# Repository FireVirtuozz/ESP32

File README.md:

# ESP32 RC car and Rust ground station

A 1/10 RC car (Supra MK5 body, 3D printed chassis) built from scratch: a custom PCB, two ESP32-S3 running C firmware (ESP-IDF), and a Rust ground station that drives the car, shows the sensors and builds a 2D map (SLAM).

## What it does

- **Drive** the car with a gamepad over Wi-Fi (UDP), with configurable acceleration profiles, an emergency brake and front / rear obstacle blocking
- **Sense**: IMU, lidar, ToF, ultrasonic, GNSS, camera (JPG stream), wheel encoder, battery voltage and motor current
- **Ground station** (laptop): egui GUI, record and replay, OTA updates, odometry, 2D SLAM (NDT and ICP)
- **Remote**: a Tailscale relay forwards the data without the GUI

## How it fits together

```
 sensors / motor / servo
          |
   custom PCB (KiCad)
          |
  ESP32-S3 control (C, ESP-IDF) --.
                                   >--- UDP over Wi-Fi ---> rust_station (laptop, egui)
  ESP32-S3 camera  (C, ESP-IDF) --'                          |  odometry, SLAM, record / replay
          ^                                                   |
          '------------- commands (gamepad, every 30 ms) -----'
```

## Repo

| Folder | Content |
|---|---|
| [`esp_project`](esp_project) | ESP-IDF firmware (C): the libraries and the car firmware |
| [`rust_station`](rust_station) | Rust ground station ([`station`](rust_station/station)) and AI training ([`train_ia`](rust_station/train_ia)) |
| [`hardware`](hardware) | KiCad project of the PCB, power and wiring |

The same ESP-IDF libraries were also used for a Zigbee home hub (ESP32-C6). They are easy to reuse to test sensors, MQTT, OTA, ESP-NOW, encryption or Wi-Fi.

## Hardware

| Part | Model |
|---|---|
| Body / chassis | Supra MK5 1/10, 3D printed chassis (Dukedoks design), full PLA |
| Battery | LiPo 7.3 V, 3000 mAh, 25C |
| Motor / driver | Brushed 550 (21T), BTS7960 H-bridge |
| Steering | MG996R servo |
| Boards | ESP32-S3 N16R8 (control), ESP32-S3 (camera) |
| Camera | OV5640, 120° lens <!-- TODO: check, it was in the TODO list of my notes --> |
| Sensors | BNO085 IMU, D500 lidar, BZ181 GNSS, TOF400C (front), HC-SR04 (front / rear), ACS758 50 A current sensor, FC-33 optical encoder |
| Other | KY-006 passive buzzer, 2x Mini560 Pro buck converters (5 V / 3.3 V) |

Power and wiring details are in [`hardware`](hardware).

## Status

| Done | In progress / planned |
|---|---|
| UDP control and telemetry, OTA | Check the camera with sleep / framerate |
| Acceleration profiles, emergency brake | Wi-Fi hotspot setup, cleaner logs |
| Odometry (IMU + encoder) | Chunked grid, better log-odds |
| 2D SLAM (NDT, ICP) | Sensor fusion (accelerometer / odometry / camera) to detect and correct slipping |
| Record and replay | Second, phase-shifted encoder to get the direction |
| egui GUI, Tailscale relay | Pure Pursuit with waypoints |
| ESP-NOW library (not used on the car yet) | Exploration algorithm on the grid |
| | Rear camera |
| | AI for control |
| | Custom controller (ESP-NOW) |
| | Real Tamiya TT02 chassis, new clean body (PETG / clear PETG / TPU) |

## Docker (ESP-IDF)

You can use the minimal Dockerfile of this repo (Windows-friendly) or the one from [Espressif](https://github.com/espressif/esp-idf/blob/master/tools/docker/Dockerfile).

```bash
docker build -t esp32-idf .
docker run -it --rm --network host --device=/dev/ttyUSB0 -v $(pwd):/workspace esp32-idf
```

<details>
<summary>Windows + WSL (USB passthrough)</summary>

Share the USB device from Windows to WSL:

```bash
ls /dev/ttyUSB*
usbipd list
usbipd bind --busid 2-3
usbipd attach --wsl --busid 2-3
```

Then launch the container from PowerShell:

```bash
usbipd attach --wsl --busid 2-3

# using /mnt/c from WSL (works, but slow)
cd D:\ESP32
wsl
docker run -it --rm --network host --device=/dev/ttyUSB0 -v $(pwd):/workspace esp32-idf

# better for performance: stay inside WSL and sync files with GitHub
wsl
cd ~/projects/ESP32
docker run -it --rm --network host -v $(pwd):/workspace esp32-idf:latest
```

</details>

## Run the station

See [`rust_station`](rust_station) for the details of the station.

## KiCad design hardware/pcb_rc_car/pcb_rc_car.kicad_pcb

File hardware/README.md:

# hardware

KiCad project of the PCB of the RC car, with the power and wiring of the car.

<!-- TODO: add the schematic (PDF or PNG) and a render of the PCB here -->

## Files

<!-- TODO: list what is in this folder, ex: kicad/ (project), gerbers/, schematic.pdf, pcb.png -->

## Power

```
Battery -> switch -> ACS758 -> 2x Wago (14 AWG)

Wago 1: battery 7.3 V in, 2200 uF polymer cap, BTS7960 B+ (then M+/M- to the motor),
        voltage divider (10 k / 5.1 k + 100 nF) to the battery ADC, link to Wago 2
Wago 2: 7.3 V -> Mini560 5 V (-> PCB)
                 Mini560 3.3 V (-> PCB)
```

PCB power inputs have a 100 nF ceramic cap + a polymer cap in parallel (470 uF on 5 V, 220 uF on 3.3 V). Tracks are 1.5 mm wide on 5 V and 1 mm on 3.3 V.

## PCB connections

| Module | Supply | Signals |
|---|---|---|
| BNO085 | 3.3 V | I2C, INT (GPIO), RST (GPIO) |
| TOF400C | 3.3 V | I2C |
| ACS758 | 3.3 V | analog out -> 1 k + 100 nF filter -> ADC |
| FC-33 | 3.3 V | pulse -> PCNT |
| KY-006 | 3.3 V | LEDC |
| BTS7960 | 5 V | R_PWM / L_PWM (LEDC), R_EN and L_EN tied to 3.3 V |
| MG996R | 5 V | PWM (LEDC) |
| D500 lidar | 5 V | UART RX only, motor PWM pin tied to GND |
| BZ181 GNSS | 5 V | UART RX / TX |
| HC-SR04 | 5 V | trigger (GPIO), echo (GPIO, 1 k / 2 k divider to 3.3 V) |

The I2C bus has a footprint for 4.7 k pull-ups on SDA and SCL. The camera board is powered from the PCB through a 2.54 mm header (with a 100 nF + 10 uF filter).

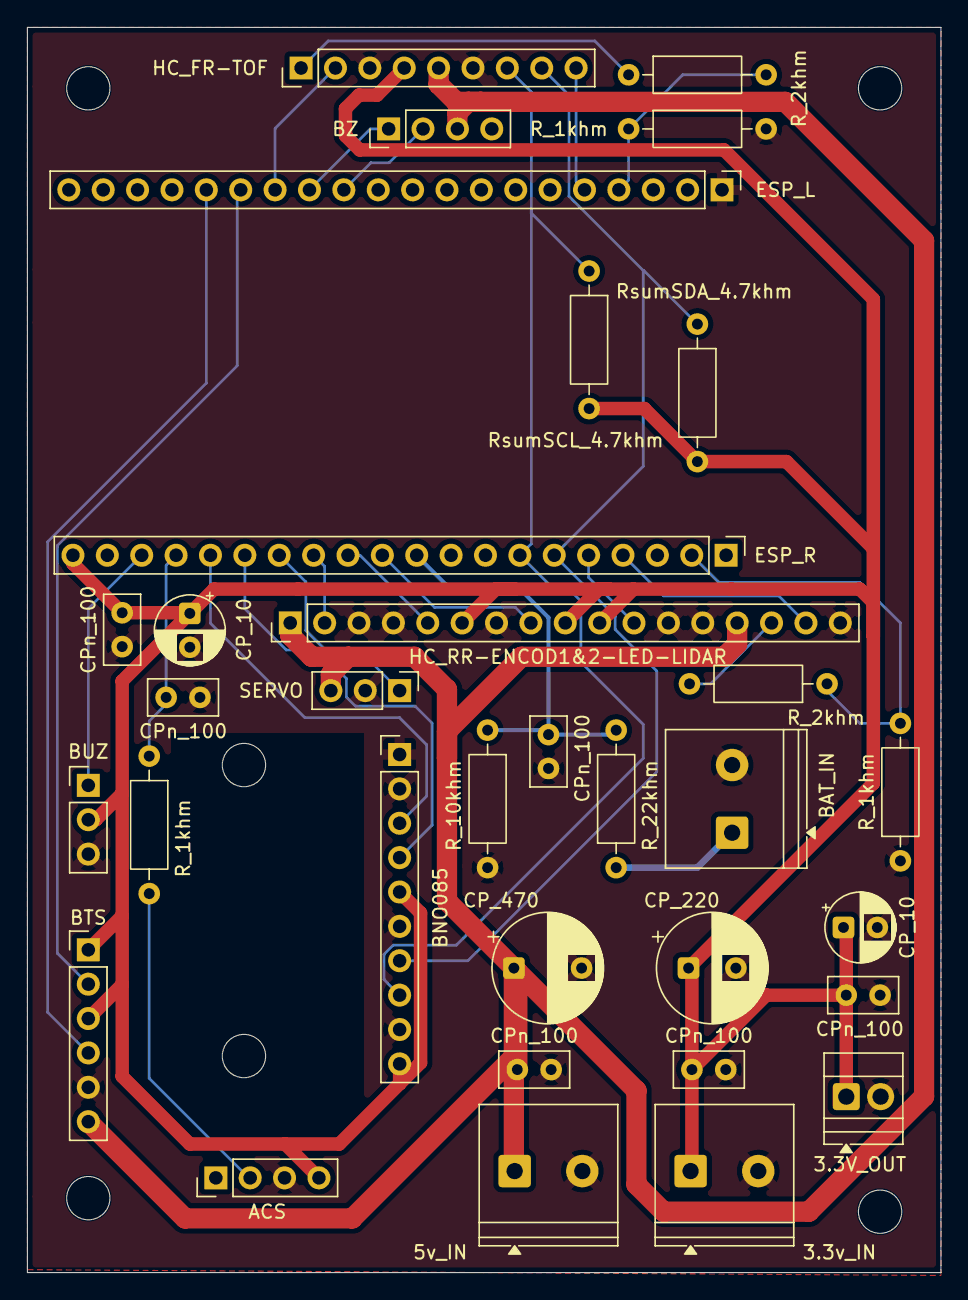
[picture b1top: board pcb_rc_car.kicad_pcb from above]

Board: 2 copper layers, 67.5 x 92.0 mm, 33 parts (0 on the bottom side), 28 nets.

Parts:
3.3V_OUT: TerminalBlock_Xinya_XY308-2.54-2P_1x02_P2.54mm_Ho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; TerminalBlock_Xinya_XY308-2.54-2P_1x02_P2.54mm_Horizontal
3.3v_IN, 5v_IN: TerminalBlock_Philmore_TB132_1x02_P5.00mm_Horizon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; TerminalBlock_Philmore_TB132_1x02_P5.00mm_Horizontal
ACS: PinHeader_1x04_P2.54mm_Vertical
BAT_IN: TerminalBlock_Philmore_TB132_1x02_P5.00mm_Horizon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; TerminalBlock_Philmore_TB132_1x02_P5.00mm_Horizontal
BNO085: BNO085; PinHeader_1x10_P2.54mm_Vertical
BTS: PinHeader_1x06_P2.54mm_Vertical
BUZ: PinHeader_1x03_P2.54mm_Vertical
BZ: PinHeader_1x04_P2.54mm_Vertical
CP_10, CP_10#2: CP_Radial_D5.0mm_P2.50mm
CP_220: CP_Radial_D8.0mm_P3.50mm
CP_470: CP_Radial_D8.0mm_P5.00mm
CPn_100, CPn_100#2, CPn_100#3, CPn_100#4, CPn_100#5, CPn_100#6: C_Disc_D5.0mm_W2.5mm_P2.50mm
ESP_L: ESP_LEFT; PinHeader_1x20_P2.54mm_Vertical
ESP_R: ESP_RIGHT; PinHeader_1x20_P2.54mm_Vertical
HC_FR-TOF: PinHeader_1x09_P2.54mm_Vertical
HC_RR-ENCOD1&2-LED-LIDAR: PinHeader_1x17_P2.54mm_Vertical
R_1khm, R_1khm#2, R_1khm#3, R_2khm, R_2khm#2, R_10khm, R_22khm: R_Axial_DIN0207_L6.3mm_D2.5mm_P10.16mm_Horizontal
RsumSCL_4.7khm: R_Axial_DIN0207_L6.3mm_D2.5mm_P10.16mm_Horizontal
RsumSDA_4.7khm: R_Axial_DIN0207_L6.3mm_D2.5mm_P10.16mm_Horizontal
SERVO: PinHeader_1x03_P2.54mm_Vertical

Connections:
3.3v: 3.3V_OUT.1, 3.3v_IN.1, ACS.4, BNO085.5, BNO085.10, BTS.1, BTS.3, BUZ.2, CP_10.1, CP_10#2.1, CP_220.1, CPn_100#2.1, CPn_100#4.1, CPn_100#5.2, ESP_R.20 (3.3v), HC_FR-TOF.4, HC_RR-ENCOD1&2-LED-LIDAR.6, HC_RR-ENCOD1&2-LED-LIDAR.9, HC_RR-ENCOD1&2-LED-LIDAR.10, RsumSCL_4.7khm.2, RsumSDA_4.7khm.2
5v: 5v_IN.1, BTS.6, BZ.3, CP_470.1, CPn_100.2, HC_FR-TOF.5, HC_RR-ENCOD1&2-LED-LIDAR.1, HC_RR-ENCOD1&2-LED-LIDAR.14, SERVO.3
adc_bat: CPn_100#6.1, ESP_R.10, R_10khm.1, R_22khm.2
adc_curr: CPn_100#3.1, ESP_R.17, R_1khm#2.1
bat_in: BAT_IN.1, R_22khm.1
data_led: ESP_R.5, HC_RR-ENCOD1&2-LED-LIDAR.11
gnd: 3.3V_OUT.2, 3.3v_IN.2, 5v_IN.2, ACS.3, BAT_IN.2, BNO085.1, BNO085.2, BNO085.6, BNO085.9, BTS.5, BUZ.3, BZ.4, CP_10.2, CP_10#2.2, CP_220.2, CP_470.2, CPn_100.1, CPn_100#2.2, CPn_100#3.2, CPn_100#4.2, CPn_100#5.1, CPn_100#6.2, ESP_L.1, HC_FR-TOF.3, HC_FR-TOF.6, HC_RR-ENCOD1&2-LED-LIDAR.3, HC_RR-ENCOD1&2-LED-LIDAR.4, HC_RR-ENCOD1&2-LED-LIDAR.7, HC_RR-ENCOD1&2-LED-LIDAR.12, HC_RR-ENCOD1&2-LED-LIDAR.13, HC_RR-ENCOD1&2-LED-LIDAR.17, R_1khm.2, R_1khm#3.1, R_10khm.2, SERVO.2
gpio_encod: ESP_R.11, HC_RR-ENCOD1&2-LED-LIDAR.8
gpio_encod_2: ESP_R.12, HC_RR-ENCOD1&2-LED-LIDAR.5
hc_front_3.3v: ESP_L.4, R_1khm.1, R_2khm.2
hc_front_5v: HC_FR-TOF.1, R_2khm.1
hc_front_trig: ESP_L.14, HC_FR-TOF.2
hc_rear_3.3v: ESP_R.2, R_1khm#3.2, R_2khm#2.1
hc_rear_5v: HC_RR-ENCOD1&2-LED-LIDAR.15, R_2khm#2.2
hc_rear_trig: ESP_R.13, HC_RR-ENCOD1&2-LED-LIDAR.2
i2c_scl: BNO085.8, ESP_R.7, HC_FR-TOF.7, RsumSCL_4.7khm.1
i2c_sda: BNO085.7, ESP_R.6, HC_FR-TOF.8, RsumSDA_4.7khm.1
int_bno: BNO085.4, ESP_R.15
int_tof: ESP_L.5, HC_FR-TOF.9
l_pwm: BTS.2, ESP_L.15
out_acs: ACS.2, R_1khm#2.2
pwm_buz: BUZ.1, ESP_R.18
r_pwm: BTS.4, ESP_L.16
rst_bno: BNO085.3, ESP_R.16
rx_bz: BZ.2, ESP_L.12
rx_lid: ESP_R.4, HC_RR-ENCOD1&2-LED-LIDAR.16
servo_pwm: ESP_R.14, SERVO.1
tx_bz: BZ.1, ESP_L.13
